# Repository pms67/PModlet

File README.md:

# PModlet
 PMOD PCB with USB-to-UART converter and IMU (MPU-6050, I2C) for FPGAs.

You can order this board (incl. SMT assembly) at [https://www.jlcpcb.com/RPH](https://www.jlcpcb.com/RPH). Gerber and assembly files are in the relevant repo folders.

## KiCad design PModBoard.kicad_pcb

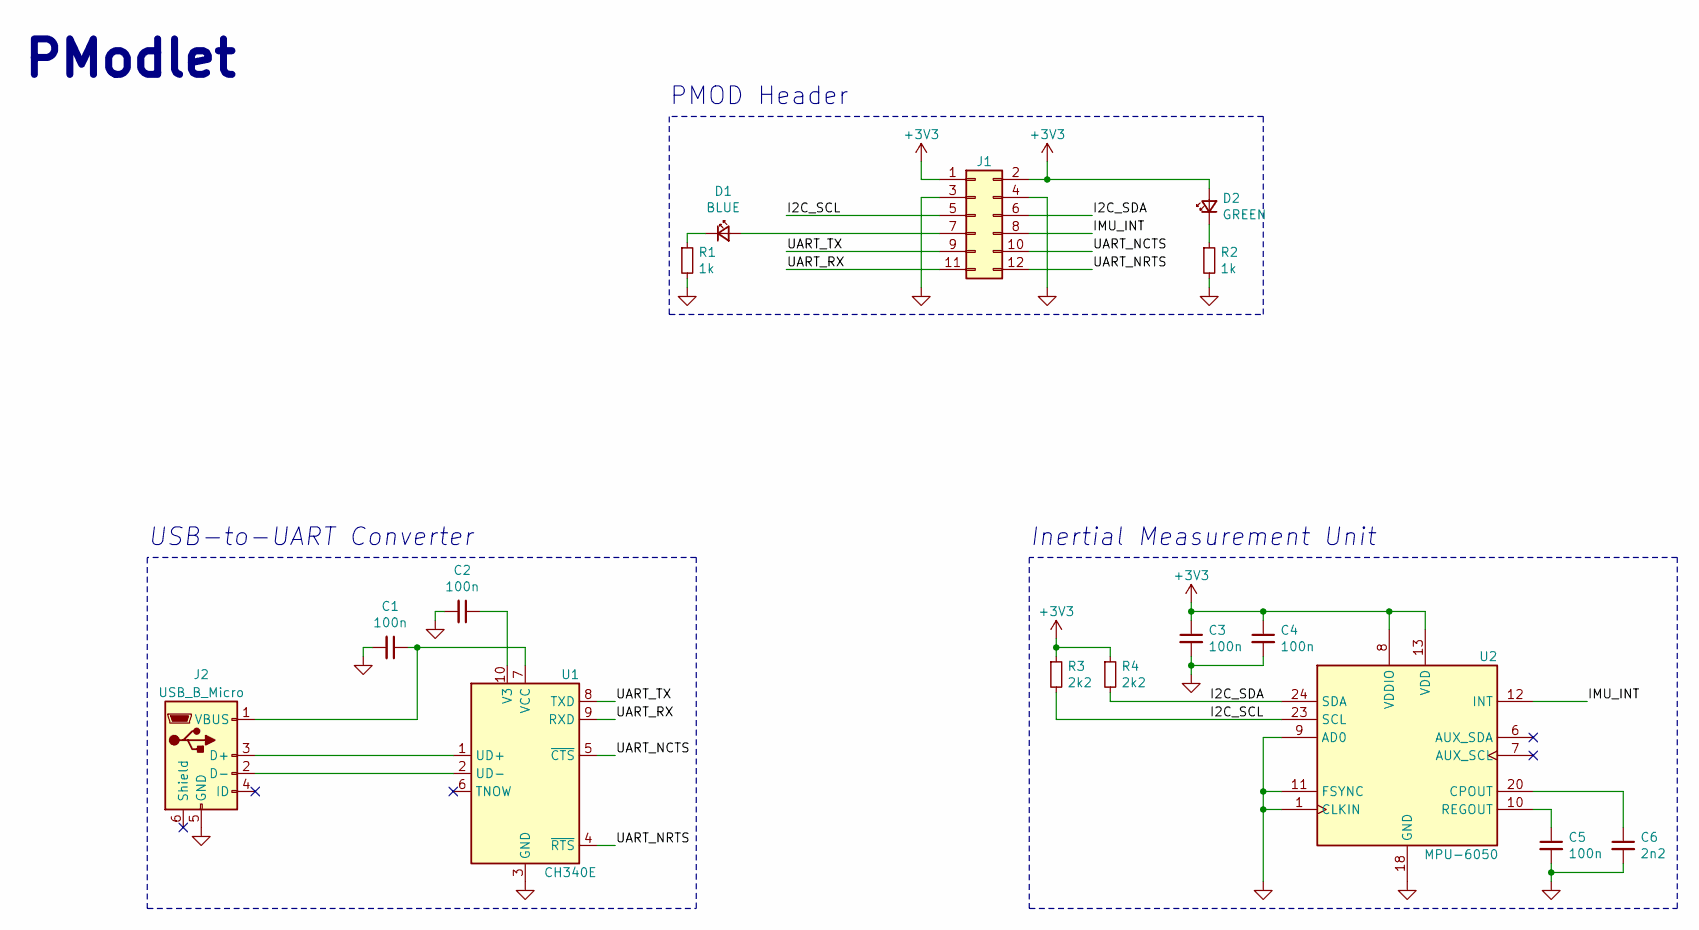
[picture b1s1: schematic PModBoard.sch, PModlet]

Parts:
C1, C2, C3, C4, C5: 100n; C_0402_1005Metric
C6: 2n2; C_0402_1005Metric
D1: BLUE; LED_0603_1608Metric
D2: GREEN; LED_0603_1608Metric
J1: Conn_02x06_Odd_Even; PinHeader_2x06_P2.54mm_Horizontal
J2: USB_B_Micro; MicroXNJ
R1, R2: 1k; R_0402_1005Metric
R3, R4: 2k2; R_0402_1005Metric
U1: CH340E; MSOP-10_3x3mm_P0.5mm
U2: MPU-6050; InvenSense_QFN-24_4x4mm_P0.5mm

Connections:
+3V3: C3.1, C4.1, D2.2 (A), J1.1, J1.2, R3.1, R4.1, U2.8 (VDDIO), U2.13 (VDD)
/I2C_SCL: J1.5, R3.2, U2.23 (SCL)
/I2C_SDA: J1.6, R4.2, U2.24 (SDA)
/IMU_INT: J1.8, U2.12 (INT)
/UART_NCTS: J1.10, U1.5 (~CTS)
/UART_NRTS: J1.12, U1.4 (~RTS)
/UART_RX: J1.11, U1.9 (RXD)
/UART_TX: J1.9, U1.8 (TXD)
GND: C1.2, C2.2, C3.2, C4.2, C5.2, C6.2, J1.3, J1.4, J2.5 (GND), R1.2, R2.2, U1.3 (GND), U2.1 (CLKIN), U2.9 (AD0), U2.11 (FSYNC), U2.18 (GND)
unnamed: C1.1, J2.1 (VBUS), U1.7 (VCC)
unnamed: C2.1, U1.10 (V3)
unnamed: C5.1, U2.10 (REGOUT)
unnamed: C6.1, U2.20 (CPOUT)
unnamed: D1.1 (K), R1.1
unnamed: D1.2 (A), J1.7
unnamed: D2.1 (K), R2.1
unnamed: J2.2 (D-), U1.2 (UD-)
unnamed: J2.3 (D+), U1.1 (UD+)

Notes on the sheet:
PMOD Header
USB-to-UART Converter
Inertial Measurement Unit
PModlet

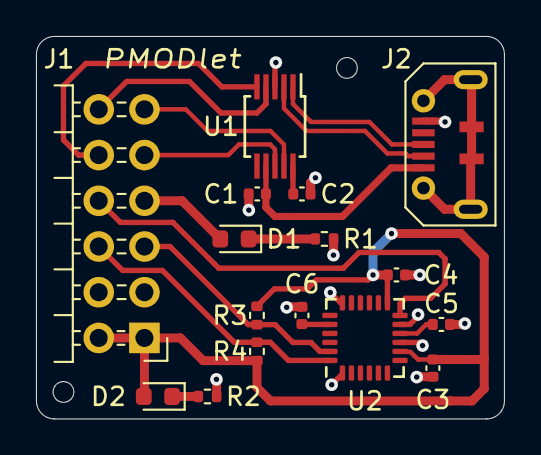
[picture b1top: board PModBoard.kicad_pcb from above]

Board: 2 copper layers, 26.0 x 21.2 mm, 16 parts (0 on the bottom side), 18 nets.

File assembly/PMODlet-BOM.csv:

"Designator","Quantity","Value","Cmp name","Footprint","Description","Vendor","LCSC Part #"
"C1, C2, C3, C4, C5, ","5","100n","C_Small","Capacitor_SMD:C_0402_1005Metric","Unpolarized capacitor, small symbol","","C1525"
"C6, ","1","2n2","C_Small","Capacitor_SMD:C_0402_1005Metric","Unpolarized capacitor, small symbol","","C1531"
"D1, ","1","BLUE","LED_Small","LED_SMD:LED_0603_1608Metric","Light emitting diode, small symbol","","C72041"
"D2, ","1","GREEN","LED_Small","LED_SMD:LED_0603_1608Metric","Light emitting diode, small symbol","","C72043"
"J1, ","1","Conn_02x06_Odd_Even","Conn_02x06_Odd_Even","Connector_PinHeader_2.54mm:PinHeader_2x06_P2.54mm_Horizontal","Generic connector, double row, 02x06, odd/even pin numbering scheme (row 1 odd numbers, row 2 even numbers), script generated (kicad-library-utils/schlib/autogen/connector/)","","C124388"
"J2, ","1","USB_B_Micro","USB_B_Micro","BluePhil-Footprints:MicroXNJ","USB Micro Type B connector","","C404969"
"R1, R2, ","2","1k","R_Small","Resistor_SMD:R_0402_1005Metric","Resistor, small symbol","","C11702"
"R3, R4, ","2","2k2","R_Small","Resistor_SMD:R_0402_1005Metric","Resistor, small symbol","","C25879"
"U1, ","1","CH340E","CH340E","Package_SO:MSOP-10_3x3mm_P0.5mm","USB serial converter, UART, MSOP-10","","C99652"
"U2, ","1","MPU-6050","MPU-6050","Sensor_Motion:InvenSense_QFN-24_4x4mm_P0.5mm","InvenSense 6-Axis Motion Sensor, Gyroscope, Accelerometer, I2C","","C24112"

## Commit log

2021-07-06 Initial commit.
